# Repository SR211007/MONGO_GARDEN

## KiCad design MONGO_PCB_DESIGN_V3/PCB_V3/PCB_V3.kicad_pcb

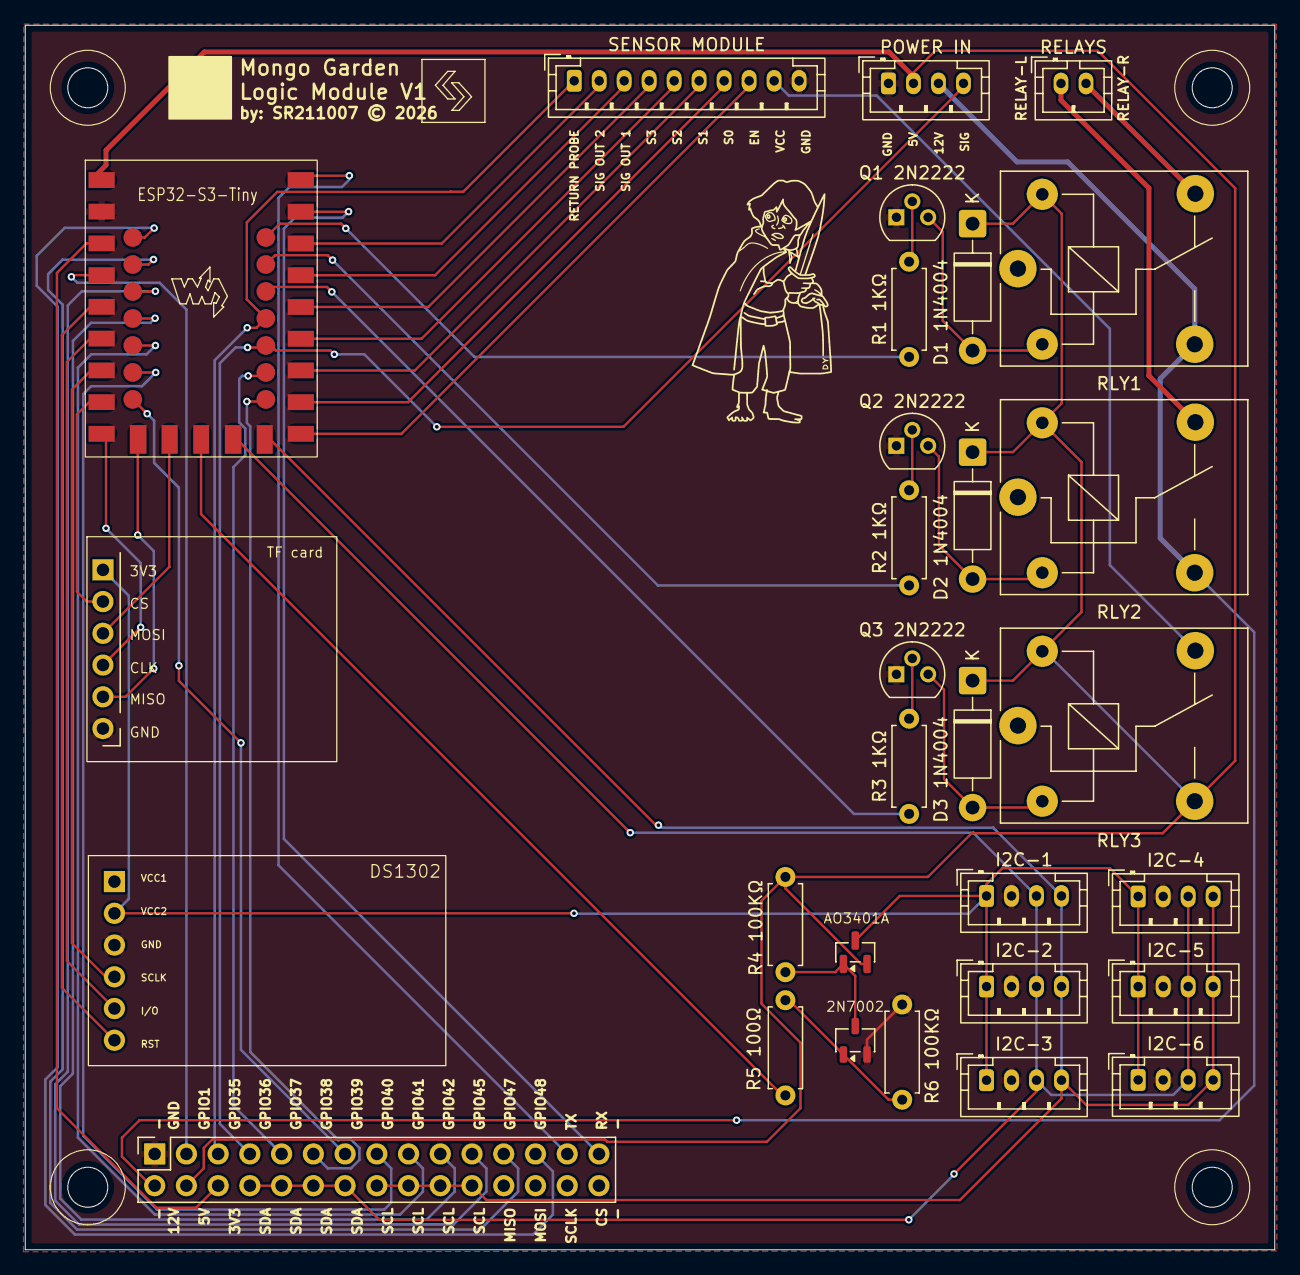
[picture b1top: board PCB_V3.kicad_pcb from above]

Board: 2 copper layers, 100.0 x 98.0 mm, 28 parts (0 on the bottom side), 17 nets.

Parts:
2N7002: SOT-23-3
AO3401A: SOT-23
D1 1N4004, D2 1N4004, D3 1N4004: D_DO-41_SOD81_P10.16mm_Horizontal
DS1302: DS1302
I2C-1, I2C-2, I2C-3, I2C-4, I2C-5, I2C-6: JST_PH_B4B-PH-K_1x04_P2.00mm_Vertical
POWER IN: JST_PH_B4B-PH-K_1x04_P2.00mm_Vertical
Q1 2N2222, Q2 2N2222, Q3 2N2222: TO-92
R1 1KΩ, R2 1KΩ, R3 1KΩ, R4 100KΩ, R5 100Ω, R6 100KΩ: R_Axial_DIN0207_L6.3mm_D2.5mm_P7.62mm_Horizontal
RELAYS: JST_PH_B2B-PH-K_1x02_P2.00mm_Vertical
RLY1, RLY2, RLY3: Relay_SPDT_SANYOU_SRD_Series_Form_C
SENSOR MODULE: JST_PH_B10B-PH-K_1x10_P2.00mm_Vertical
TF card: MICROSD

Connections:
5V: AO3401A.2, D1 1N4004.1, D2 1N4004.1, D3 1N4004.1, POWER IN.2, R4 100KΩ.2, RLY1.5, RLY2.5, RLY3.3, RLY3.5
5V_RAIL: AO3401A.3, DS1302.2, I2C-1.1, I2C-2.1, I2C-3.1, I2C-4.1, I2C-5.1, I2C-6.1, TF card.6
12V: POWER IN.3, RLY1.3, RLY2.3
GATE_2N7002_PULLDOWN: 2N7002.1, R5 100Ω.1, R6 100KΩ.1
GATE_AO3401A_PULLUP: 2N7002.3, AO3401A.1, R4 100KΩ.1
GND: 2N7002.2, DS1302.3, I2C-1.2, I2C-2.2, I2C-3.2, I2C-4.2, I2C-5.2, I2C-6.2, POWER IN.1, Q1 2N2222.1, Q2 2N2222.1, Q3 2N2222.1, R6 100KΩ.2, SENSOR MODULE.10, TF card.1
Q1-D1: D1 1N4004.2, Q1 2N2222.3, RLY1.2
Q2-D2: D2 1N4004.2, Q2 2N2222.3, RLY2.2
Q3-D3: D3 1N4004.2, Q3 2N2222.3, RLY3.2
R1-Q1: Q1 2N2222.2, R1 1KΩ.2
R2-Q2: Q2 2N2222.2, R2 1KΩ.2
R3-Q3: Q3 2N2222.2, R3 1KΩ.2
RELAY-L: RELAYS.1, RLY2.4
RELAY-R: RELAYS.2, RLY1.4
SCL: I2C-1.4, I2C-2.4, I2C-3.4, I2C-4.4, I2C-5.4, I2C-6.4
SDA: I2C-1.3, I2C-2.3, I2C-3.3, I2C-4.3, I2C-5.3, I2C-6.3
VCC_CONECTOR_MODULE: RLY3.4, SENSOR MODULE.9

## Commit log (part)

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2026-02-18 --test
2026-02-18 añadida funcion barometro y su setup
2026-02-19 cambios estéticos y de comentarios
2026-02-19 UI file created in python
2026-02-22 ignore
2026-02-22 gitignore updated
2026-02-23 no changes
2026-02-24 PCB FORLDER CREATED
2026-02-24 webSocket system implemented -testing in process-
2026-02-24 some changes
2026-02-25 AP changes _not working_
2026-02-25 changes on AP _not working_
2026-02-26 MIGRATION TO PLATFORM IO
2026-02-26 libs added
2026-02-26 fixing things
2026-02-26 working...
2026-04-16 startMqttConfigInCloud
2026-05-14 PCB work
2026-05-14 PCB modif
2026-05-18 some work on pcb
2026-05-18 pcb modfng
2026-05-18 Create LICENSE

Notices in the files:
MONGO_PCB_DESIGN_V3/PCB_V3/PCB_V3.kicad_pcb:
by: SR211007 © 2026
